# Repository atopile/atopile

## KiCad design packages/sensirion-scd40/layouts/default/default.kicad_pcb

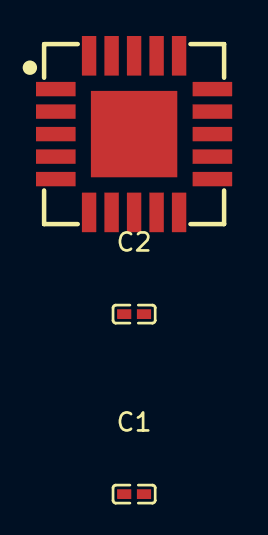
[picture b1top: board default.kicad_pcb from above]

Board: 2 copper layers, 3 parts (0 on the bottom side), 3 nets, no tracks yet.

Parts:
C1, C2: 100nF ±10% 16V X7R; C0402
U1: LGA-20_L10.1-W10.1-P1.25-TL

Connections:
DNC: U1.1, U1.2, U1.3, U1.4, U1.5, U1.8, U1.11, U1.12, U1.13, U1.14, U1.15, U1.16, U1.17, U1.18
VDD: C1.1, C2.1, U1.7, U1.19
gnd: C1.2, C2.2, U1.6, U1.20, U1.21

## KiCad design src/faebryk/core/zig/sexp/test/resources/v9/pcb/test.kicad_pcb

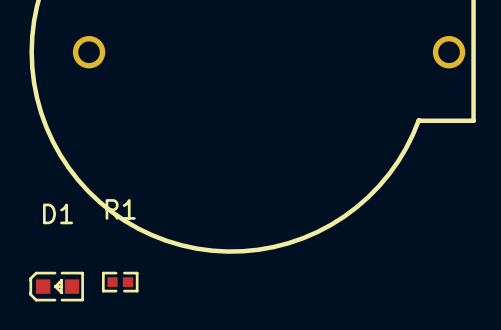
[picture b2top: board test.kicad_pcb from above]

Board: 2 copper layers, 3 parts (0 on the bottom side), 3 nets, no tracks yet.

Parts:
B1: ButtonCell; BAT-TH_BS-02-A1AJ010
D1: LED; LED0603-RD-YELLOW
R1: 40.2Ω; R0402

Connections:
B1-1-R1-2: B1.1, R1.2
B1-2-D1-2: B1.2, D1.2
D1-1-R1-1: D1.1, R1.1
